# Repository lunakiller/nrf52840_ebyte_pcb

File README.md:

# nRF52840 Adaptor PCB
Breadboard compatible adaptor PCB for Ebyte E73-2G4M08S1C with Nordic Semiconductor's nRF52840 MCU. Contains 3.3V voltage regulator.

Designed in KiCad, gerbers for JLCPCB available.

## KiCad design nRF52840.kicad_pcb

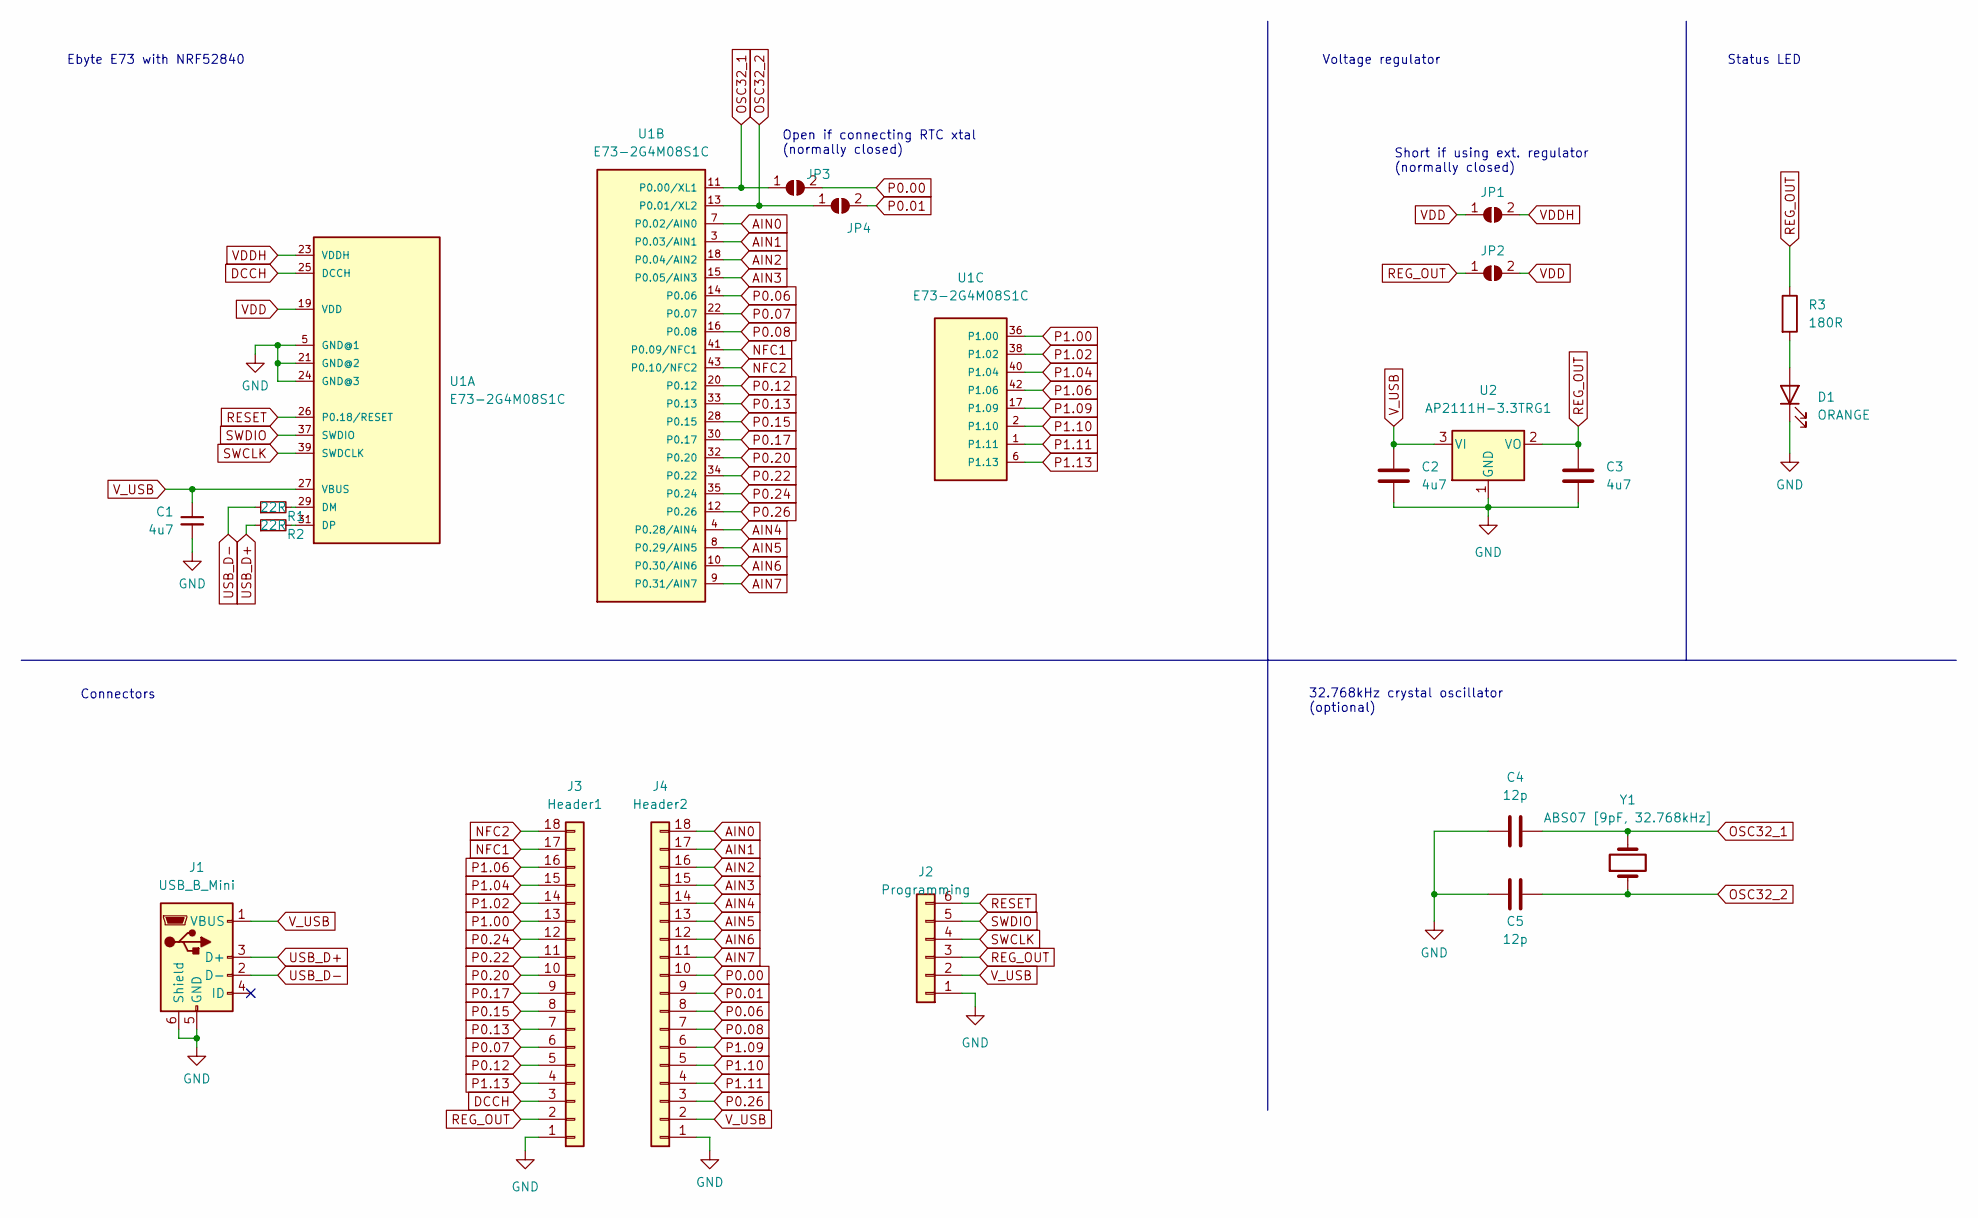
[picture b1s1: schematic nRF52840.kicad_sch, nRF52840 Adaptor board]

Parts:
C1, C2, C3: 4u7; C_0603_1608Metric_Pad1.08x0.95mm_HandSolder
C4, C5: 12p; C_0603_1608Metric_Pad1.08x0.95mm_HandSolder
D1: ORANGE; LED_0603_1608Metric_Pad1.05x0.95mm_HandSolder
J1: USB_B_Mini; USB_Mini-B_Lumberg_2486_01_Horizontal
J2: Programming; PinHeader_1x06_P2.54mm_Vertical
J3: Header1; PinHeader_1x18_P2.54mm_Vertical
J4: Header2; PinHeader_1x18_P2.54mm_Vertical
JP1, JP2, JP3, JP4: SolderJumper_2_Open; SolderJumper-2_P1.3mm_Open_TrianglePad1.0x1.5mm
R1, R2: 22R; R_0603_1608Metric_Pad0.98x0.95mm_HandSolder
R3: 180R; R_0603_1608Metric_Pad0.98x0.95mm_HandSolder
U1: E73-2G4M08S1C
U2: AP2111H-3.3TRG1; SOT-223-3_TabPin2
Y1: ABS07 [9pF, 32.768kHz]; Crystal_SMD_3215-2Pin_3.2x1.5mm

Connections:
AIN0: J4.18, U1.7 (P0.02/AIN0)
AIN1: J4.17, U1.3 (P0.03/AIN1)
AIN2: J4.16, U1.18 (P0.04/AIN2)
AIN3: J4.15, U1.15 (P0.05/AIN3)
AIN4: J4.14, U1.4 (P0.28/AIN4)
AIN5: J4.13, U1.8 (P0.29/AIN5)
AIN6: J4.12, U1.10 (P0.30/AIN6)
AIN7: J4.11, U1.9 (P0.31/AIN7)
DCCH: J3.3, U1.25 (DCCH)
GND: C1.2, C2.2, C3.2, C4.1, C5.1, D1.1 (K), J1.5 (GND), J1.6 (Shield), J2.1, J3.1, J4.1, U1.5 (GND@1), U1.21 (GND@2), U1.24 (GND@3), U2.1 (GND)
NFC1: J3.17, U1.41 (P0.09/NFC1)
NFC2: J3.18, U1.43 (P0.10/NFC2)
unnamed: D1.2 (A), R3.2
unnamed: R1.2, U1.29 (DM)
unnamed: R2.2, U1.31 (DP)
OSC32_1: C4.2, JP3.1 (A), U1.11 (P0.00/XL1), Y1.2
OSC32_2: C5.2, JP4.1 (A), U1.13 (P0.01/XL2), Y1.1
P0.00: J4.10, JP3.2 (B)
P0.01: J4.9, JP4.2 (B)
P0.06: J4.8, U1.14 (P0.06)
P0.07: J3.6, U1.22 (P0.07)
P0.08: J4.7, U1.16 (P0.08)
P0.12: J3.5, U1.20 (P0.12)
P0.13: J3.7, U1.33 (P0.13)
P0.15: J3.8, U1.28 (P0.15)
P0.17: J3.9, U1.30 (P0.17)
P0.20: J3.10, U1.32 (P0.20)
P0.22: J3.11, U1.34 (P0.22)
P0.24: J3.12, U1.35 (P0.24)
P0.26: J4.3, U1.12 (P0.26)
P1.00: J3.13, U1.36 (P1.00)
P1.02: J3.14, U1.38 (P1.02)
P1.04: J3.15, U1.40 (P1.04)
P1.06: J3.16, U1.42 (P1.06)
P1.09: J4.6, U1.17 (P1.09)
P1.10: J4.5, U1.2 (P1.10)
P1.11: J4.4, U1.1 (P1.11)
P1.13: J3.4, U1.6 (P1.13)
REG_OUT: C3.1, J2.3, J3.2, JP2.1 (A), R3.1, U2.2 (VO)
RESET: J2.6, U1.26 (P0.18/RESET)
SWCLK: J2.4, U1.39 (SWDCLK)
SWDIO: J2.5, U1.37 (SWDIO)
USB_D+: J1.3 (D+), R2.1
USB_D-: J1.2 (D-), R1.1
VDD: JP1.1 (A), JP2.2 (B), U1.19 (VDD)
VDDH: JP1.2 (B), U1.23 (VDDH)
V_USB: C1.1, C2.1, J1.1 (VBUS), J2.2, J4.2, U1.27 (VBUS), U2.3 (VI)

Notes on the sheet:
Voltage regulator
Short if using ext. regulator (normally closed)
Ebyte E73 with NRF52840
Status LED
32.768kHz crystal oscillator (optional)
Open if connecting RTC xtal (normally closed)
Connectors

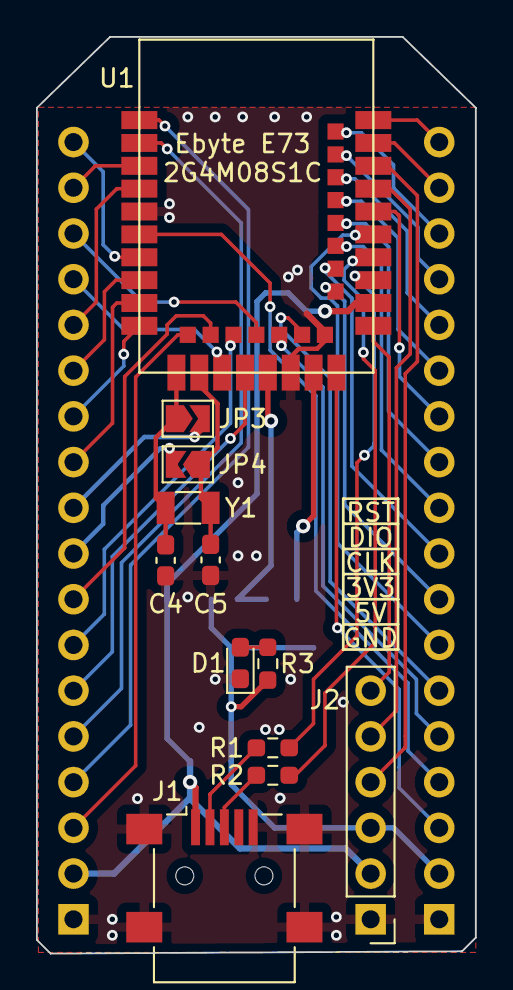
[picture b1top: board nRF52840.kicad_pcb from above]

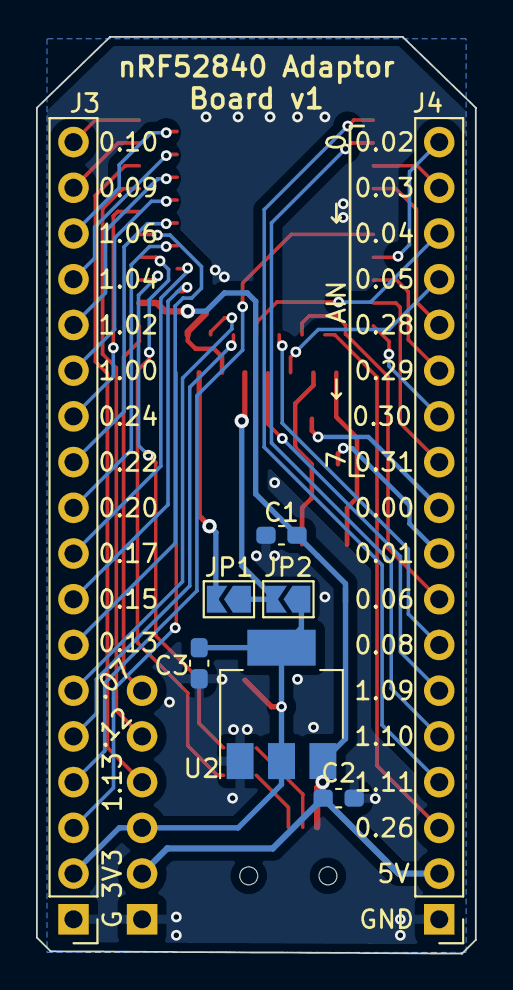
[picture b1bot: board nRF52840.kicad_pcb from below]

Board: 2 copper layers, 24.4 x 50.9 mm, 20 parts (8 on the bottom side), 47 nets.

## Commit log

2022-07-26 Upload files
2022-07-26 Small readme update
